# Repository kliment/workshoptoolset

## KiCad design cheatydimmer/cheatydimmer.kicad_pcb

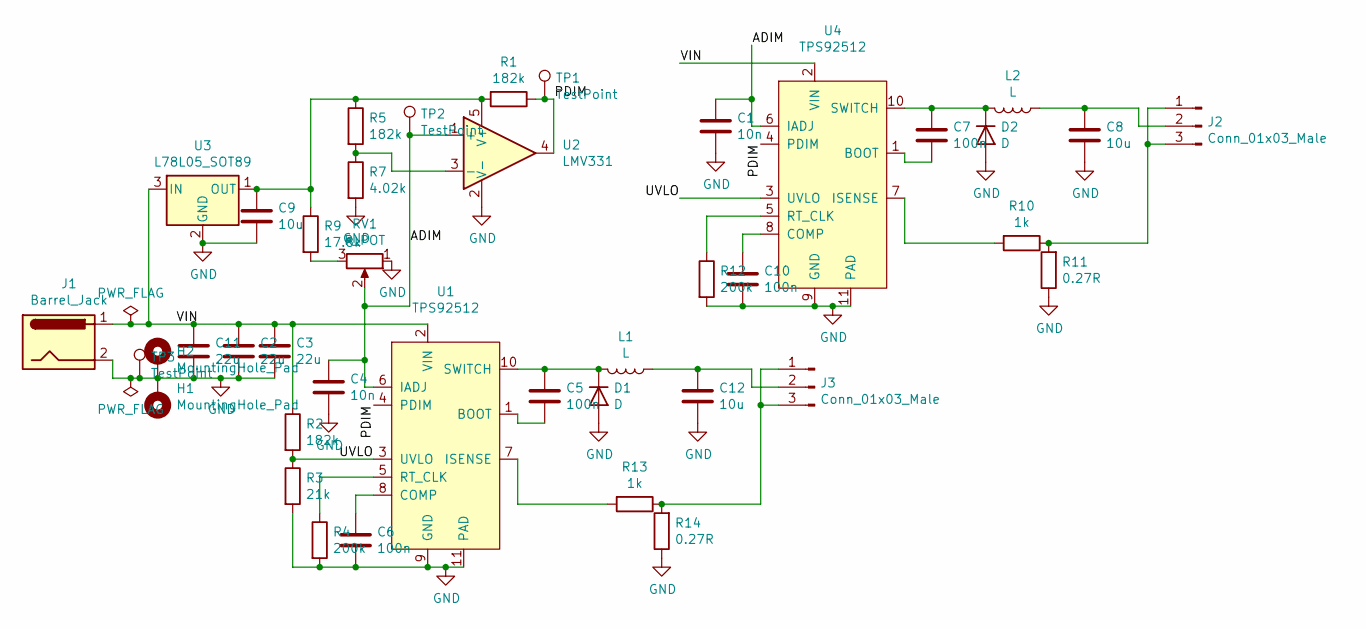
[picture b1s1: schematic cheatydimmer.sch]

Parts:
C1, C4: 10n; C_0603_1608Metric
C2, C3, C11: 22u; C_1206_3216Metric
C5, C6, C7, C10: 100n; C_0603_1608Metric
C8, C9, C12: 10u; C_0805_2012Metric
D1, D2: D; D_SMA
H1, H2: MountingHole_Pad; MountingHole_3.2mm_M3_Pad_Via
J1: Barrel_Jack; BarrelJack_Horizontal
J2, J3: Conn_01x03_Male; PinHeader_1x03_P2.54mm_Vertical
L1, L2: L; L_Sumida_CDMC6D28_7.25x6.5mm
R1, R2, R5: 182k; R_0603_1608Metric
R3: 21k; R_0603_1608Metric
R4, R12: 200k; R_0603_1608Metric
R7: 4.02k; R_0603_1608Metric
R9: 17.8k; R_0603_1608Metric
R10, R13: 1k; R_0603_1608Metric
R11, R14: 0.27R; R_1210_3225Metric
RV1: R_POT; ALPS-RS08U
TP1, TP2, TP3: TestPoint; TestPoint_Pad_1.5x1.5mm
U1, U4: TPS92512; MSOP-10-1EP_3x3mm_P0.5mm_EP1.73x1.98mm_ThermalVias
U2: LMV331; SOT-23-5
U3: L78L05_SOT89; SOT-89-3

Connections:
/ADIM: C1.1, C4.1, RV1.2, TP2.1, U1.6 (IADJ), U2.1 (+), U4.6 (IADJ)
/PDIM: R1.1, TP1.1, U1.4 (PDIM), U2.4, U4.4 (PDIM)
/UVLO: R2.2, R3.1, U1.3 (UVLO), U4.3 (UVLO)
/VIN: C2.1, C3.1, C11.1, J1.1, R2.1, U1.2 (VIN), U3.3 (IN), U4.2 (VIN)
GND: C1.2, C2.2, C3.2, C4.2, C6.2, C8.2, C9.2, C10.2, C11.2, C12.2, D1.2 (A), D2.2 (A), H1.1, H2.1, J1.2, R3.2, R4.2, R7.2, R11.1, R12.2, R14.1, RV1.1, TP3.1, U1.9 (GND), U1.11 (PAD), U2.2 (V-), U3.2 (GND), U4.9 (GND), U4.11 (PAD)
unnamed: C5.1, D1.1 (K), L1.2, U1.10 (SWITCH)
unnamed: C5.2, U1.1 (BOOT)
unnamed: C6.1, U1.8 (COMP)
unnamed: C7.1, D2.1 (K), L2.2, U4.10 (SWITCH)
unnamed: C7.2, U4.1 (BOOT)
unnamed: C8.1, J2.2, L2.1
unnamed: C9.1, R1.2, R5.1, R9.1, U2.5 (V+), U3.1 (OUT)
unnamed: C10.1, U4.8 (COMP)
unnamed: C12.1, J3.2, L1.1
unnamed: J2.1, J2.3, R10.1, R11.2
unnamed: J3.1, J3.3, R13.1, R14.2
unnamed: R4.1, U1.5 (RT_CLK)
unnamed: R5.2, R7.1, U2.3 (-)
unnamed: R9.2, RV1.3
unnamed: R10.2, U4.7 (ISENSE)
unnamed: R12.1, U4.5 (RT_CLK)
unnamed: R13.2, U1.7 (ISENSE)

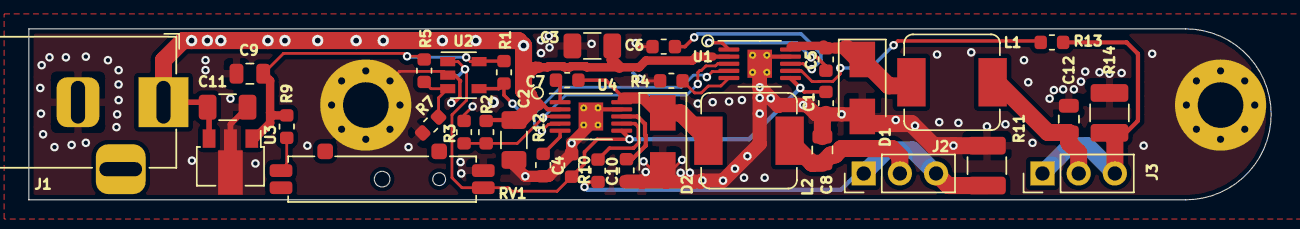
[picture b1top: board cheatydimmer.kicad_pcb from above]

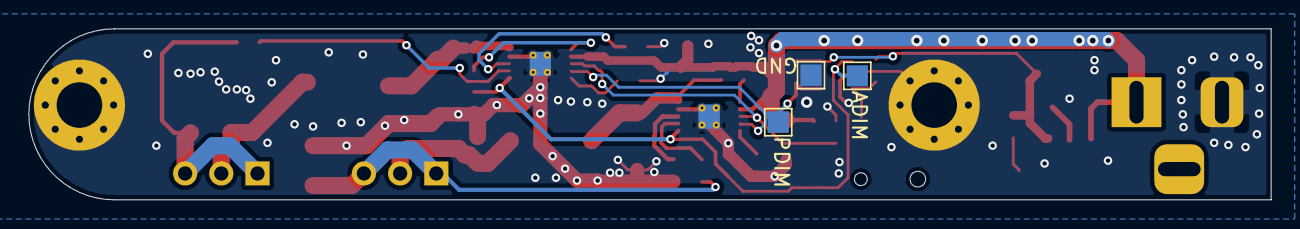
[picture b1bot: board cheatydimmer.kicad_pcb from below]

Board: 2 copper layers, 87.2 x 12.0 mm, 41 parts (3 on the bottom side), 22 nets.

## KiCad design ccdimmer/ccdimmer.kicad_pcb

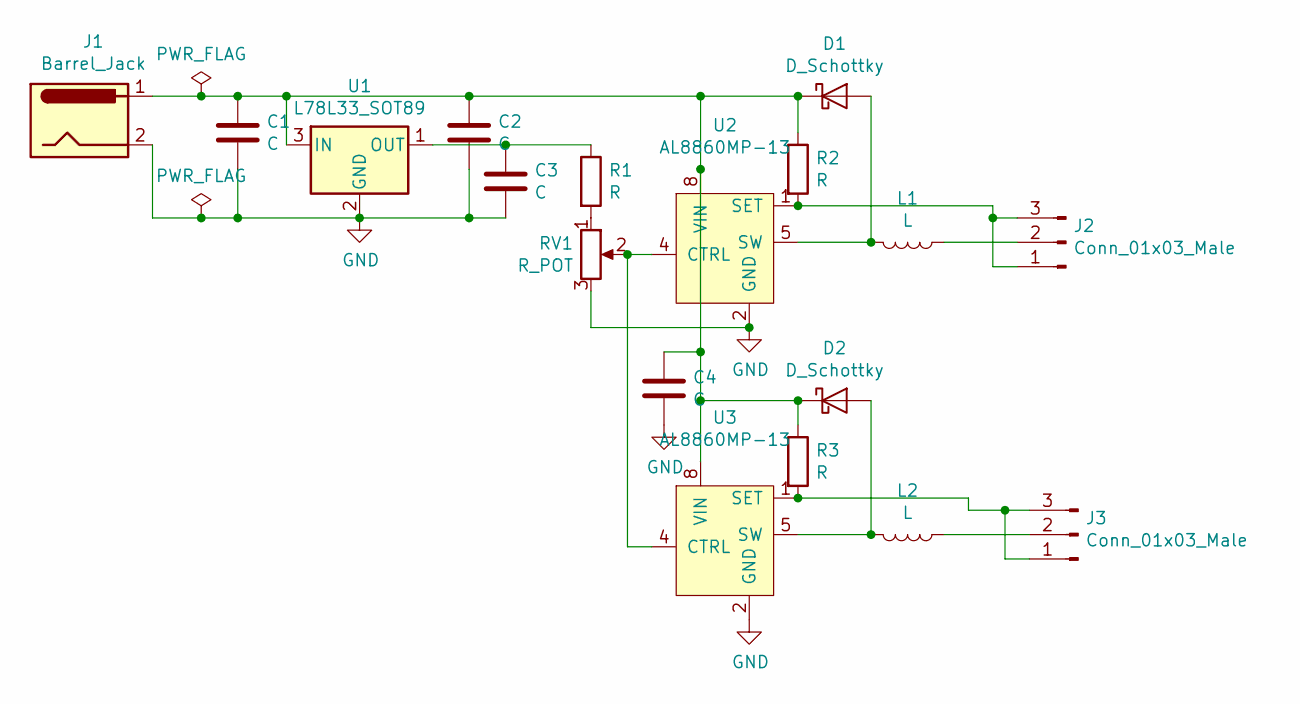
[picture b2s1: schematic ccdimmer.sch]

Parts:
C1, C2, C3, C4: C; C_0805_2012Metric
D1, D2: D_Schottky; D_SMA
J1: Barrel_Jack; BarrelJack_Horizontal
J2, J3: Conn_01x03_Male; PinHeader_1x03_P2.54mm_Vertical
L1, L2: L; L_6.3x6.3_H3
R1: R; R_0603_1608Metric
R2, R3: R; R_1206_3216Metric
RV1: R_POT; ALPS-RS08U
U1: L78L33_SOT89; SOT-89-3
U2, U3: AL8860MP-13; MSOP-8-1EP_3x3mm_P0.65mm_EP1.95x2.15mm

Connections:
GND: C1.2, C2.2, C3.2, C4.2, J1.2, RV1.3, U1.2 (GND), U2.2 (GND), U2.3 (GND), U2.9 (GND), U3.2 (GND), U3.3 (GND), U3.9 (GND)
unnamed: C1.1, C2.1, C4.1, D1.1 (K), D2.1 (K), J1.1, R2.1, R3.1, U1.3 (IN), U2.8 (VIN), U3.8 (VIN)
unnamed: C3.1, R1.1, U1.1 (OUT)
unnamed: D1.2 (A), L1.2, U2.5 (SW), U2.6 (SW)
unnamed: D2.2 (A), L2.2, U3.5 (SW), U3.6 (SW)
unnamed: J2.1, J2.3, R2.2, U2.1 (SET)
unnamed: J2.2, L1.1
unnamed: J3.1, J3.3, R3.2, U3.1 (SET)
unnamed: J3.2, L2.1
unnamed: R1.2, RV1.1
unnamed: RV1.2, U2.4 (CTRL), U3.4 (CTRL)

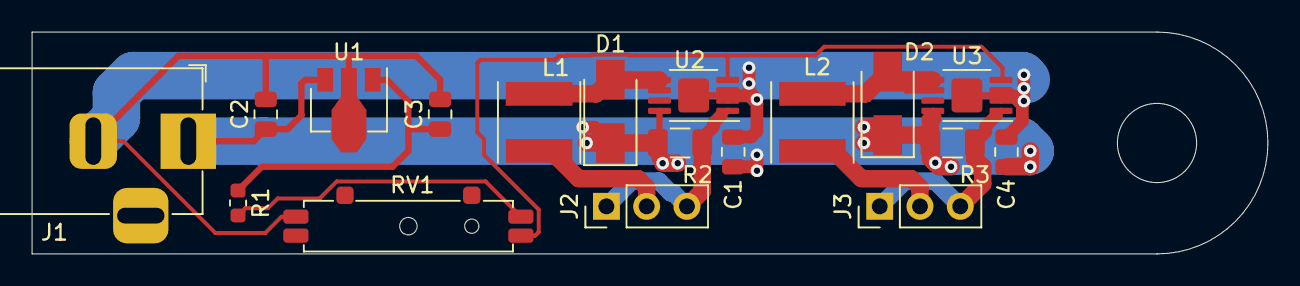
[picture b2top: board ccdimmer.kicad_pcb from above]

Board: 2 copper layers, 78.0 x 14.0 mm, 18 parts (0 on the bottom side), 11 nets.

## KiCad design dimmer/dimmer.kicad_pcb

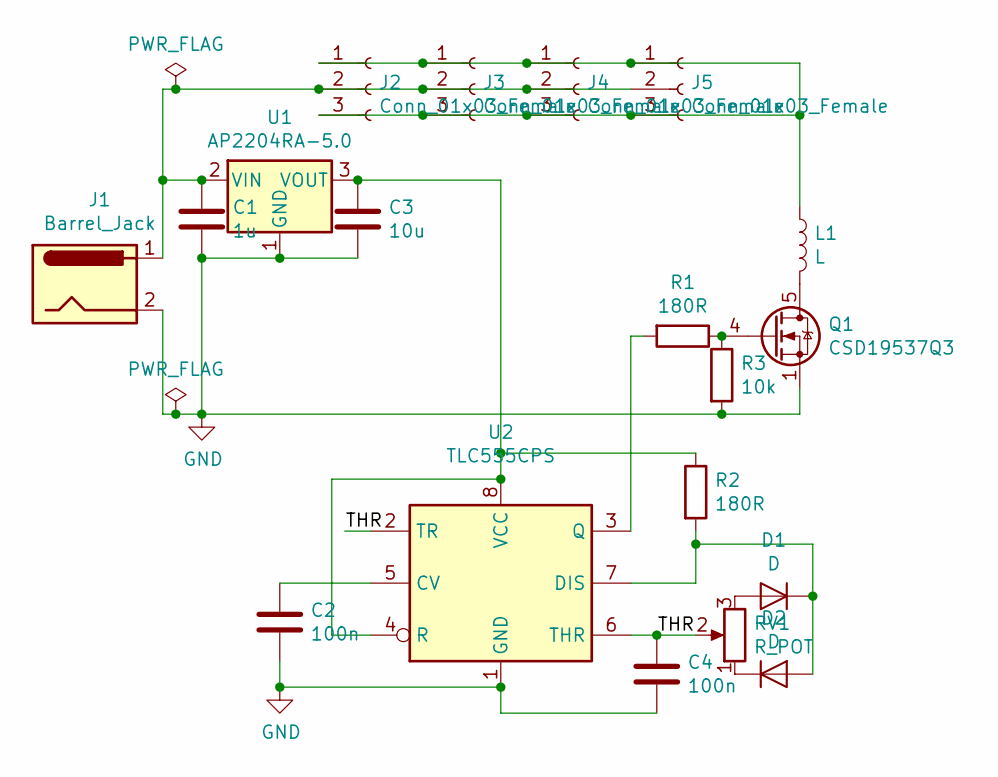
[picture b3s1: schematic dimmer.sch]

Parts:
C1: 1u; C_0603_1608Metric
C2, C4: 100n; C_0402_1005Metric
C3: 10u; C_0402_1005Metric
D1, D2: D; D_SOD-523
J1: Barrel_Jack; BarrelJack_Horizontal
J2, J3, J4, J5: Conn_01x03_Female; PinSocket_1x03_P2.54mm_Vertical
L1: L; INDUCTOR_2x1.6x1mm
Q1: CSD19537Q3; VSON-8_3.3x3.3mm_P0.65mm_NexFET
R1, R2: 180R; R_0603_1608Metric
R3: 10k; R_0603_1608Metric
RV1: R_POT; ALPS-RS08U
U1: AP2204RA-5.0; SOT-89-3
U2: TLC555CPS; TSSOP-8_3x3mm_P0.65mm

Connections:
/THR: C4.1, RV1.2, U2.2 (TR), U2.6 (THR)
GND: C1.2, C2.2, C3.2, C4.2, J1.2, Q1.1 (S), Q1.2 (S), Q1.3 (S), R3.2, U1.1 (GND), U2.1 (GND)
unnamed: C1.1, J1.1, J2.2, J3.2, J4.2, J5.2, U1.2 (VIN)
unnamed: C2.1, U2.5 (CV)
unnamed: C3.1, R2.1, U1.3 (VOUT), U2.4 (R), U2.8 (VCC)
unnamed: D1.1 (K), D2.2 (A), R2.2, U2.7 (DIS)
unnamed: D1.2 (A), RV1.3
unnamed: D2.1 (K), RV1.1
unnamed: J2.1, J2.3, J3.1, J3.3, J4.1, J4.3, J5.1, J5.3, L1.1
unnamed: L1.2, Q1.5 (D)
unnamed: Q1.4 (G), R1.1, R3.1
unnamed: R1.2, U2.3 (Q)

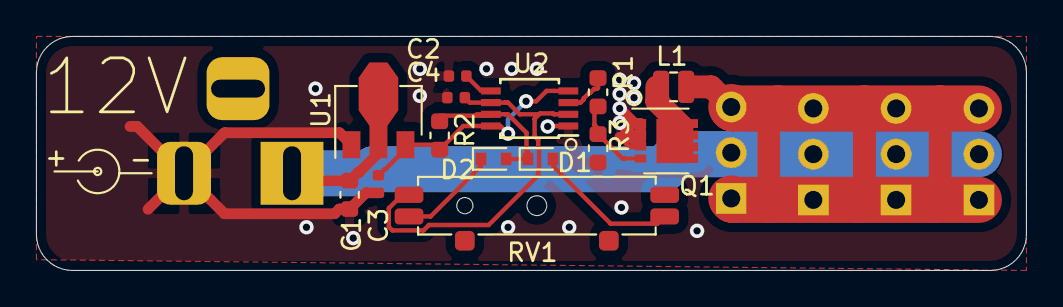
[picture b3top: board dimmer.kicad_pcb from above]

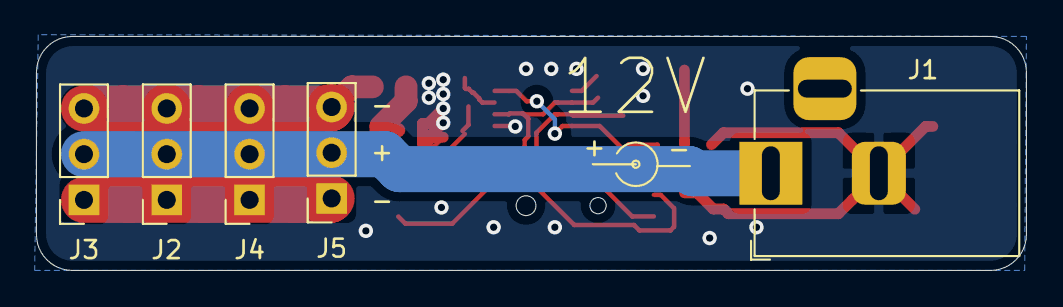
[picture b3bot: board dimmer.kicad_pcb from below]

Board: 2 copper layers, 55.0 x 13.0 mm, 19 parts (5 on the bottom side), 12 nets.

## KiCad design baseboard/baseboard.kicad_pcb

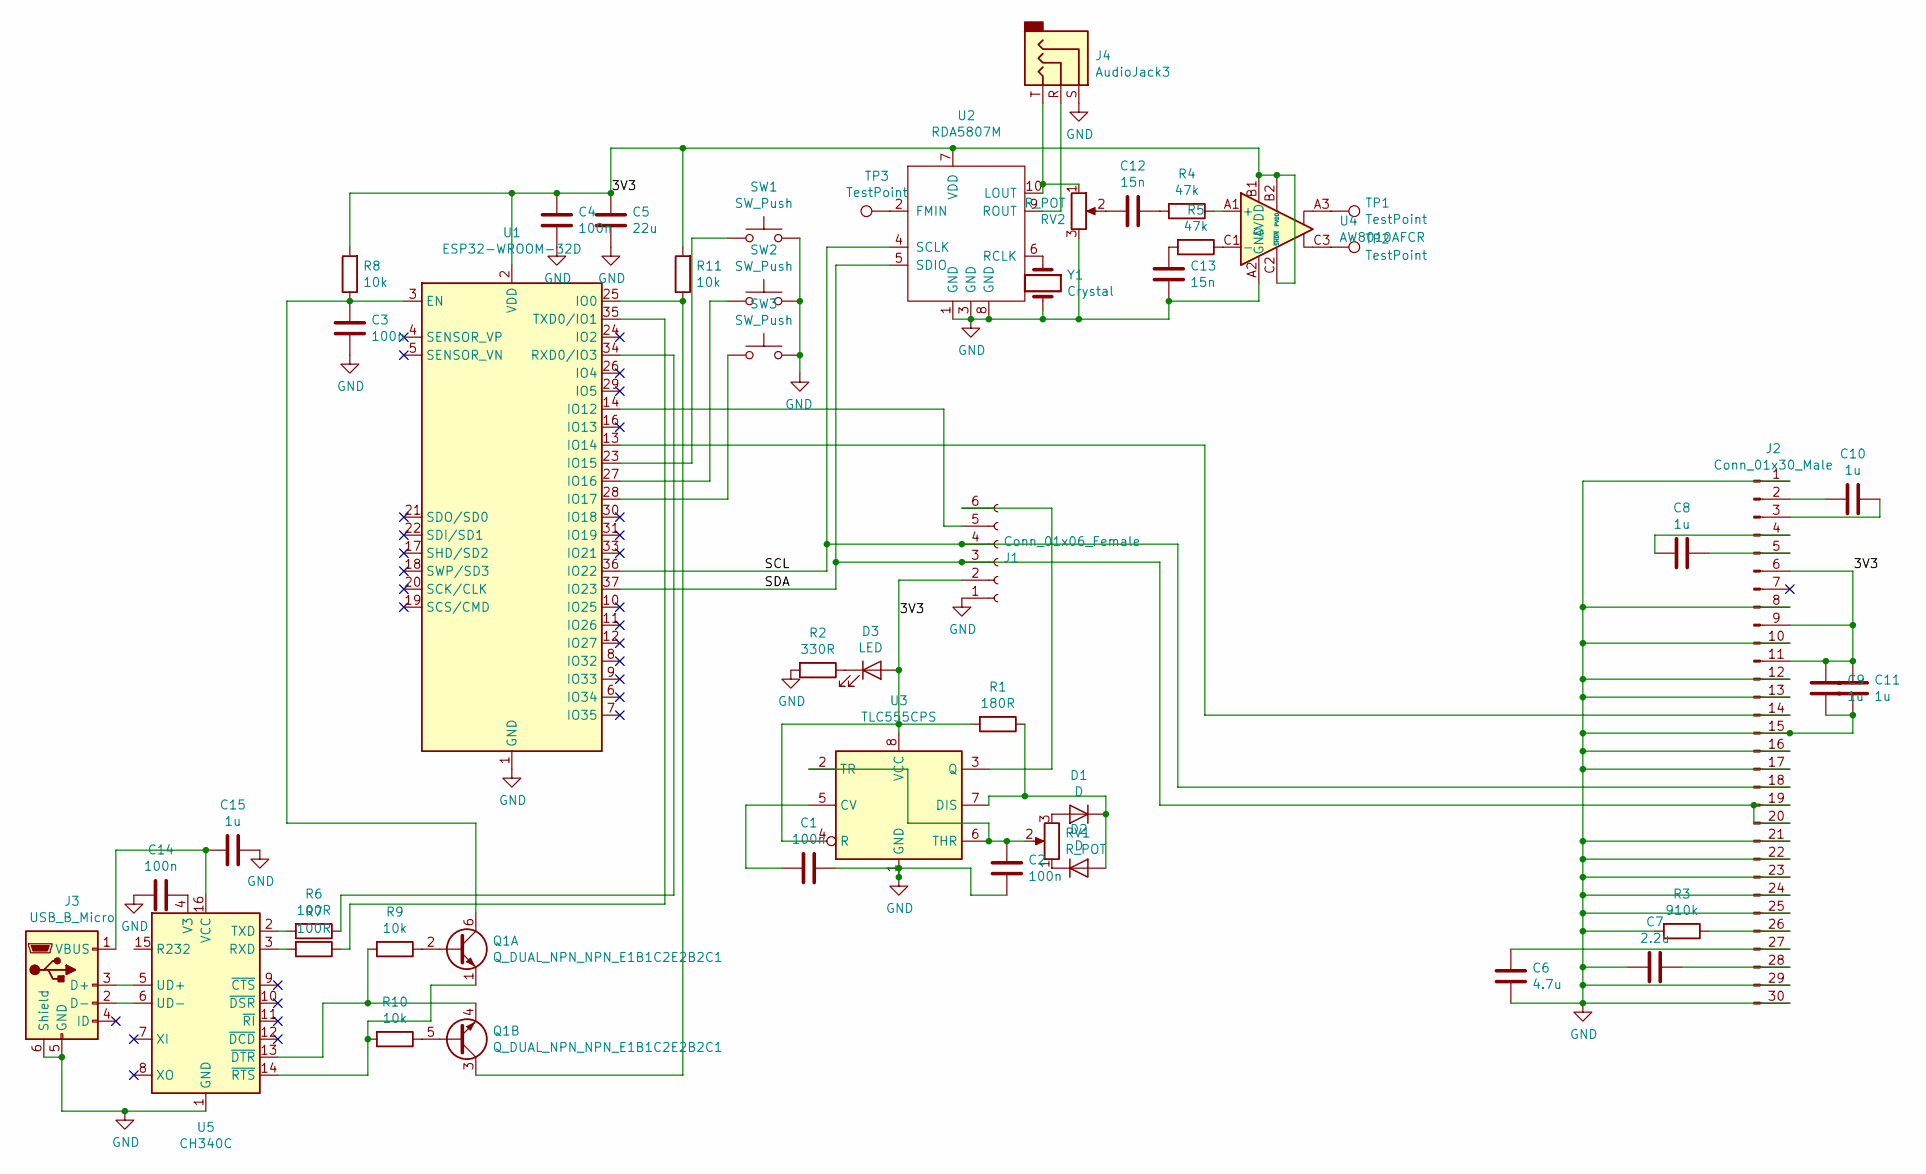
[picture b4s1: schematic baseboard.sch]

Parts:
C1, C2, C3, C4, C14: 100n; C_0402_1005Metric
C5: 22u; C_0603_1608Metric
C6: 4.7u; C_0603_1608Metric
C7: 2.2u; C_0603_1608Metric
C8, C9, C10, C11, C15: 1u; C_0402_1005Metric
C12, C13: 15n; C_0402_1005Metric
D1, D2: D; D_SOD-523
D3: LED; LED_0603_1608Metric
J1: Conn_01x06_Female; PinSocket_1x06_P2.54mm_Horizontal
J2: Conn_01x30_Male; hotbar_30x0.7
J3: USB_B_Micro; USB_Micro-B_Molex-105017-0001
J4: AudioJack3; Boom-audiojack-PJ-320B
Q1: Q_DUAL_NPN_NPN_E1B1C2E2B2C1; SOT-363_SC-70-6
R1: 180R; R_0603_1608Metric
R2: 330R; R_0603_1608Metric
R3: 910k; R_0603_1608Metric
R4, R5: 47k; R_0402_1005Metric
R6, R7: 100R; R_0402_1005Metric
R8, R9, R10, R11: 10k; R_0402_1005Metric
RV1, RV2: R_POT; ALPS-RS08U
SW1, SW2, SW3: SW_Push; 1TS003B-1600-3500A
TP1, TP2, TP3: TestPoint; TestPoint_Pad_3.0x3.0mm
U1: ESP32-WROOM-32D; ESP32-WROOM-32
U2: RDA5807M; MSOP-10_3x3mm_P0.5mm
U3: TLC555CPS; TSSOP-8_4.4x3mm_P0.65mm
U4: AW8010AFCR; Texas_DSBGA-9_1.4715x1.4715mm_Layout3x3_P0.5mm
U5: CH340C; SOIC-16_3.9x9.9mm_P1.27mm
Y1: Crystal; Crystal_SMD_3215-2Pin_3.2x1.5mm

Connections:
/3V3: C4.1, C5.1, C9.1, C11.1, D3.2 (A), J1.2, J2.6, J2.9, J2.11, R1.2, R8.2, R11.2, U1.2 (VDD), U2.7 (VDD), U3.4 (R), U3.8 (VCC), U4.B1 (AVDD), U4.B2 (PVDD), U4.C2 (~SHDN)
/SCL: J1.4, J2.18, U1.36 (IO22), U2.4 (SCLK)
/SDA: J1.3, J2.19, J2.20, U1.37 (IO23), U2.5 (SDIO)
GND: C1.1, C2.2, C3.2, C4.2, C5.2, C6.2, C7.2, C9.2, C11.2, C13.1, C14.2, C15.1, J1.1, J2.1, J2.8, J2.10, J2.12, J2.13, J2.15, J2.16, J2.17, J2.21, J2.22, J2.23, J2.24, J2.25, J2.29, J2.30, J3.5 (GND), J3.6 (Shield), J4.S, R2.2, R3.2, RV2.3, SW1.1, SW2.1, SW3.1, U1.1 (GND), U1.15 (GND), U1.38 (GND), U2.1 (GND), U2.3 (GND), U2.8 (GND), U3.1 (GND), U4.A2 (GND), U4.B3 (GND), U5.1 (GND), Y1.2
unnamed: C1.2, U3.5 (CV)
unnamed: C2.1, RV1.2, U3.2 (TR), U3.6 (THR)
unnamed: C3.1, Q1.6 (C1), R8.1, U1.3 (EN)
unnamed: C6.1, J2.27
unnamed: C7.1, J2.28
unnamed: C8.1, J2.5
unnamed: C8.2, J2.4
unnamed: C10.1, J2.3
unnamed: C10.2, J2.2
unnamed: C12.1, R4.2
unnamed: C12.2, RV2.2
unnamed: C13.2, R5.2
unnamed: C14.1, U5.4 (V3)
unnamed: C15.2, J3.1 (VBUS), U5.16 (VCC)
unnamed: D1.1 (K), D2.2 (A), R1.1, U3.7 (DIS)
unnamed: D1.2 (A), RV1.3
unnamed: D2.1 (K), RV1.1
unnamed: D3.1 (K), R2.1
unnamed: J1.5, U1.14 (IO12)
unnamed: J1.6, U3.3 (Q)
unnamed: J2.14, U1.13 (IO14)
unnamed: J2.26, R3.1
unnamed: J3.2 (D-), U5.6 (UD-)
unnamed: J3.3 (D+), U5.5 (UD+)
unnamed: J4.R, U2.9 (ROUT)
unnamed: J4.T, RV2.1, U2.10 (LOUT)
unnamed: Q1.1 (E1), R10.2, U5.14 (~RTS)
unnamed: Q1.2 (B1), R9.1
unnamed: Q1.3 (C2), R11.1, U1.25 (IO0)
unnamed: Q1.4 (E2), R9.2, U5.13 (~DTR)
unnamed: Q1.5 (B2), R10.1
unnamed: R4.1, U4.A1 (+)
unnamed: R5.1, U4.C1 (-)
unnamed: R6.1, U1.34 (RXD0/IO3)
unnamed: R6.2, U5.2 (TXD)
unnamed: R7.1, U1.35 (TXD0/IO1)
unnamed: R7.2, U5.3 (RXD)
unnamed: SW1.2, U1.23 (IO15)
unnamed: SW2.2, U1.27 (IO16)
unnamed: SW3.2, U1.28 (IO17)
unnamed: TP1.1, U4.A3
unnamed: TP2.1, U4.C3
unnamed: TP3.1, U2.2 (FMIN)
unnamed: U2.6 (RCLK), Y1.1

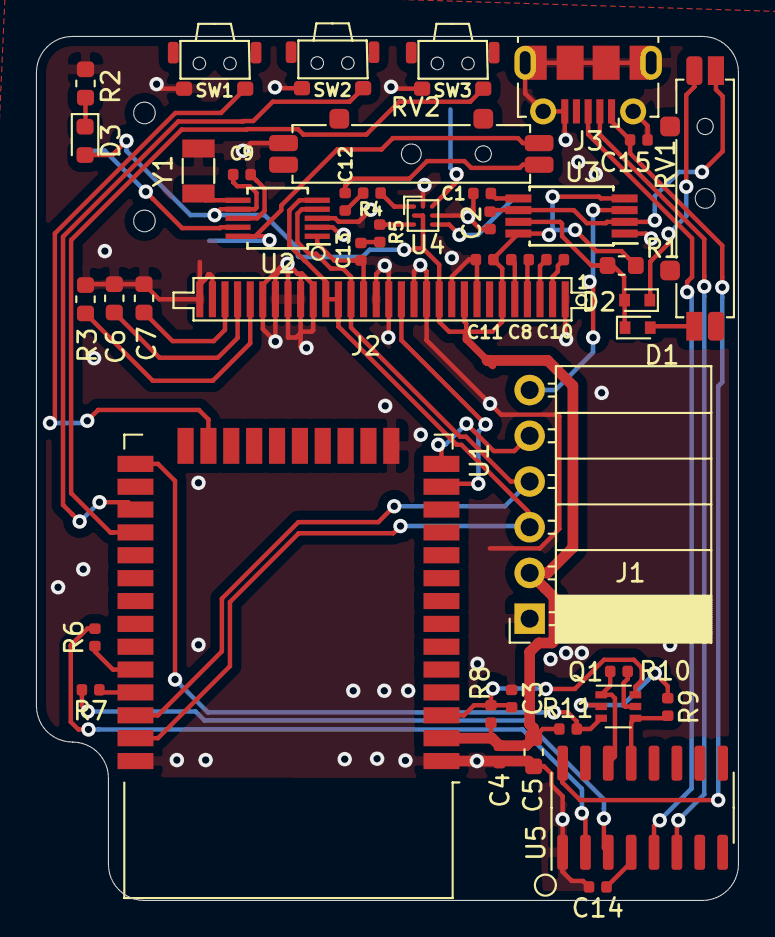
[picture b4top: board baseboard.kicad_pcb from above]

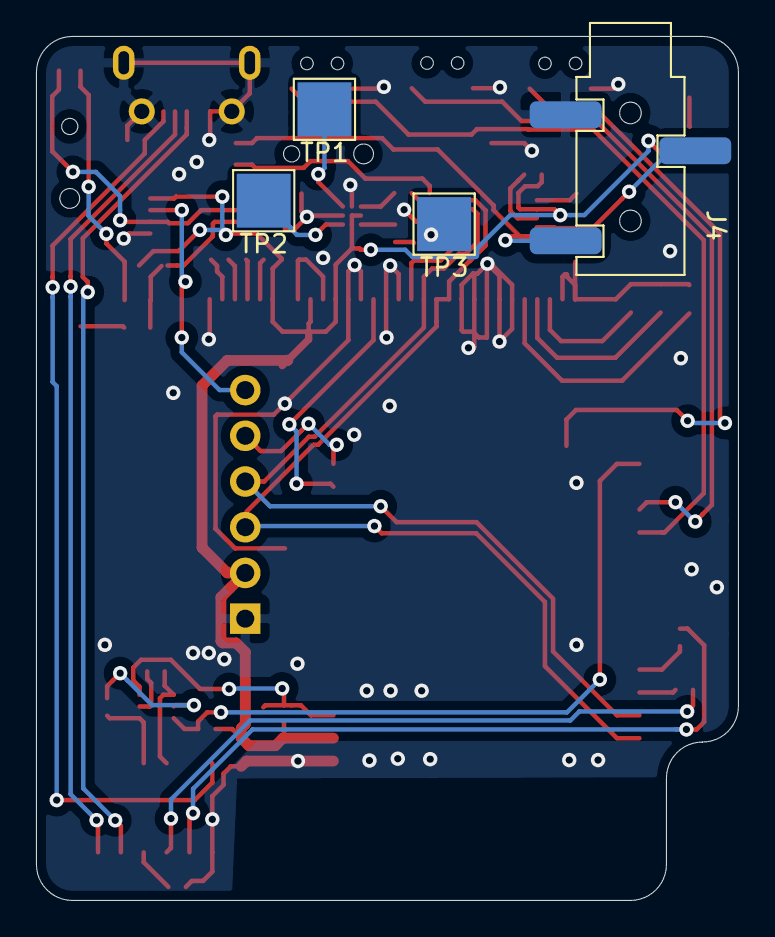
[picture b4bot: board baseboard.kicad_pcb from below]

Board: 2 copper layers, 39.0 x 48.0 mm, 48 parts (4 on the bottom side), 48 nets.

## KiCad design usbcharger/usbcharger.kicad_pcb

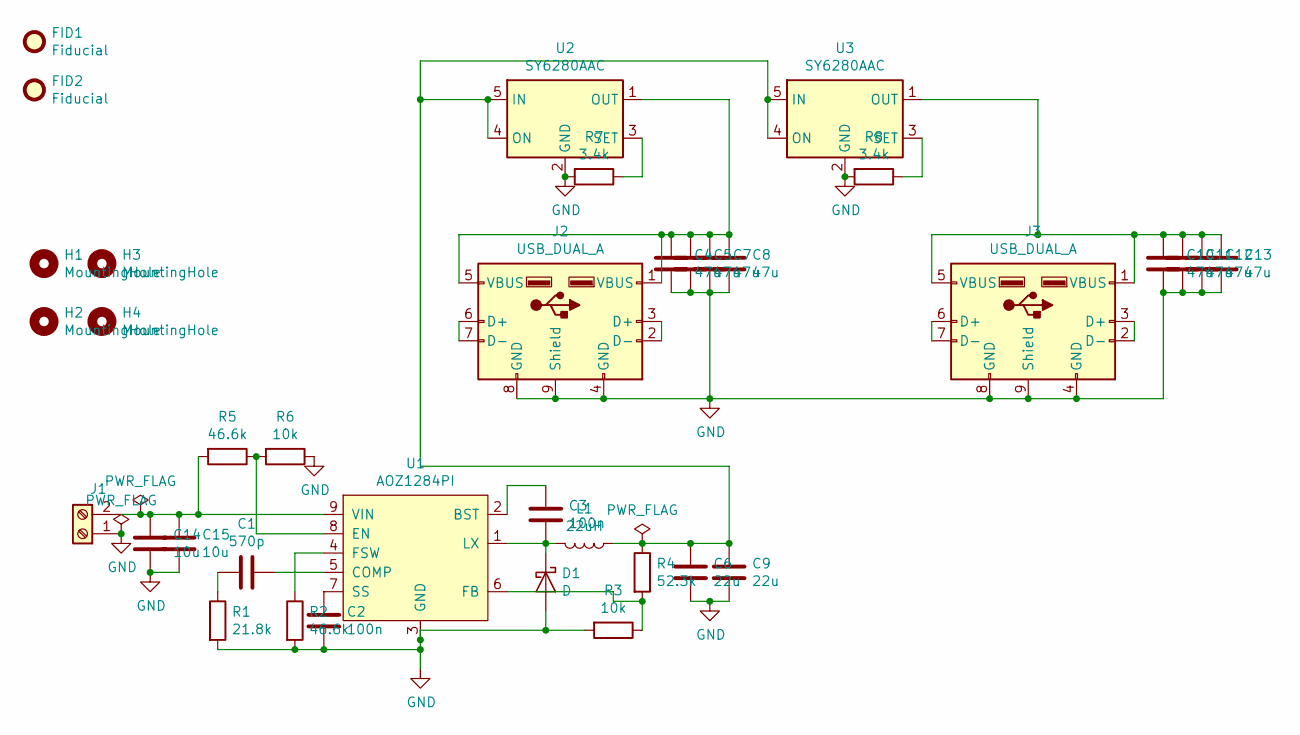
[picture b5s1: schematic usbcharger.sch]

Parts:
C1: 570p; C_0402_1005Metric
C2, C3: 100n; C_0402_1005Metric
C4, C5, C7, C8, C10, C11, C12, C13: 47u; C_1206_3216Metric
C6, C9: 22u; C_1206_3216Metric
C14, C15: 10u; C_1210_3225Metric
D1: D; D_SMA
FID1, FID2: Fiducial; Fiducial_1mm_Mask2mm
H1, H2, H3, H4: MountingHole; MountingHole_3.2mm_M3_DIN965
J1: Screw_Terminal_01x02; TerminalBlock_Phoenix_MKDS-1,5-2-5.08_1x02_P5.08mm_Horizont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
J2, J3: USB_DUAL_A; USB_A_Wuerth_61400826021_Horizontal_Stacked
L1: 22uH; L_7.3x7.3_H3.5
R1: 21.8k; R_0402_1005Metric
R2, R5: 46.6k; R_0402_1005Metric
R3, R6: 10k; R_0402_1005Metric
R4: 52.3k; R_0402_1005Metric
R7, R8: 3.4k; R_0402_1005Metric
U1: AOZ1284PI; Infineon_PG-DSO-8-43
U2, U3: SY6280AAC; SOT-23-5

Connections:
GND: C2.2, C4.2, C5.2, C6.2, C7.2, C8.2, C9.2, C10.2, C11.2, C12.2, C13.2, C14.2, C15.2, D1.2 (A), J1.1, J2.4 (GND), J2.8 (GND), J2.9 (Shield), J3.4 (GND), J3.8 (GND), J3.9 (Shield), R1.2, R2.2, R3.2, R6.1, R7.2, R8.2, U1.3 (GND), U2.2 (GND), U3.2 (GND)
unnamed: C1.1, U1.5 (COMP)
unnamed: C1.2, R1.1
unnamed: C2.1, U1.7 (SS)
unnamed: C3.1, U1.2 (BST)
unnamed: C3.2, D1.1 (K), L1.2, U1.1 (LX)
unnamed: C4.1, C5.1, C7.1, C8.1, J2.1 (VBUS), J2.5 (VBUS), U2.1 (OUT)
unnamed: C6.1, C9.1, L1.1, R4.1, U2.4 (ON), U2.5 (IN), U3.4 (ON), U3.5 (IN)
unnamed: C10.1, C11.1, C12.1, C13.1, J3.1 (VBUS), J3.5 (VBUS), U3.1 (OUT)
unnamed: C14.1, C15.1, J1.2, R5.2, U1.9 (VIN)
unnamed: J2.2 (D-), J2.3 (D+)
unnamed: J2.6 (D+), J2.7 (D-)
unnamed: J3.2 (D-), J3.3 (D+)
unnamed: J3.6 (D+), J3.7 (D-)
unnamed: R2.1, U1.4 (FSW)
unnamed: R3.1, R4.2, U1.6 (FB)
unnamed: R5.1, R6.2, U1.8 (EN)
unnamed: R7.1, U2.3 (SET)
unnamed: R8.1, U3.3 (SET)

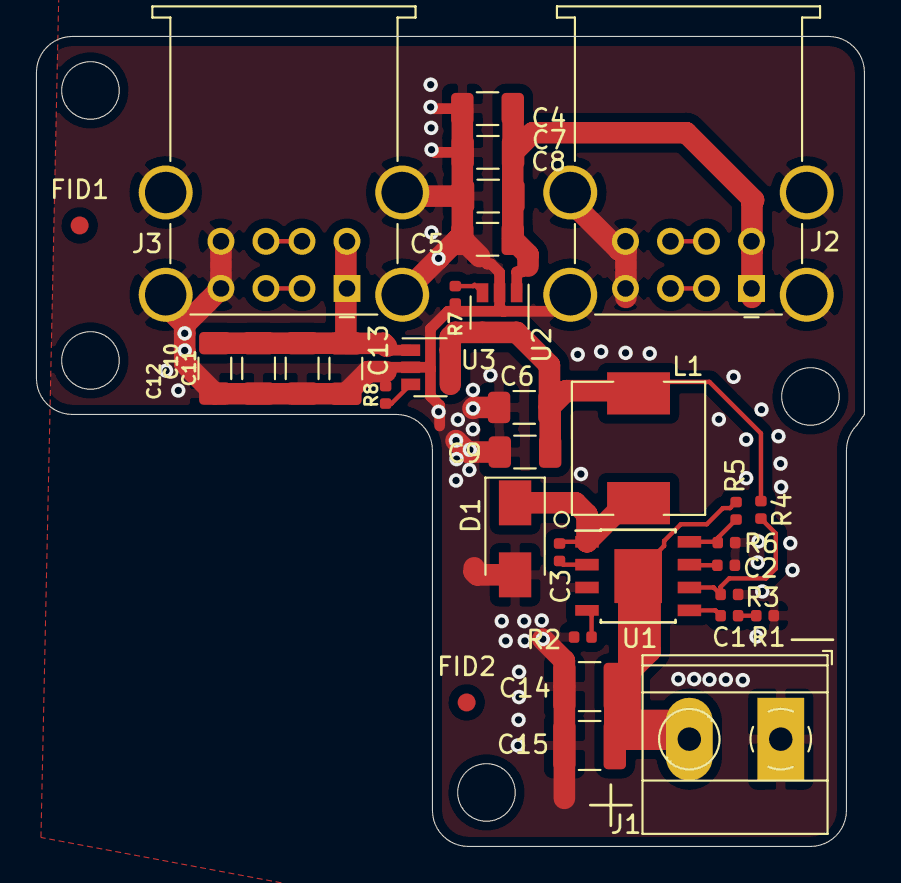
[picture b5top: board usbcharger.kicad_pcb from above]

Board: 2 copper layers, 46.0 x 45.0 mm, 37 parts (0 on the bottom side), 19 nets.

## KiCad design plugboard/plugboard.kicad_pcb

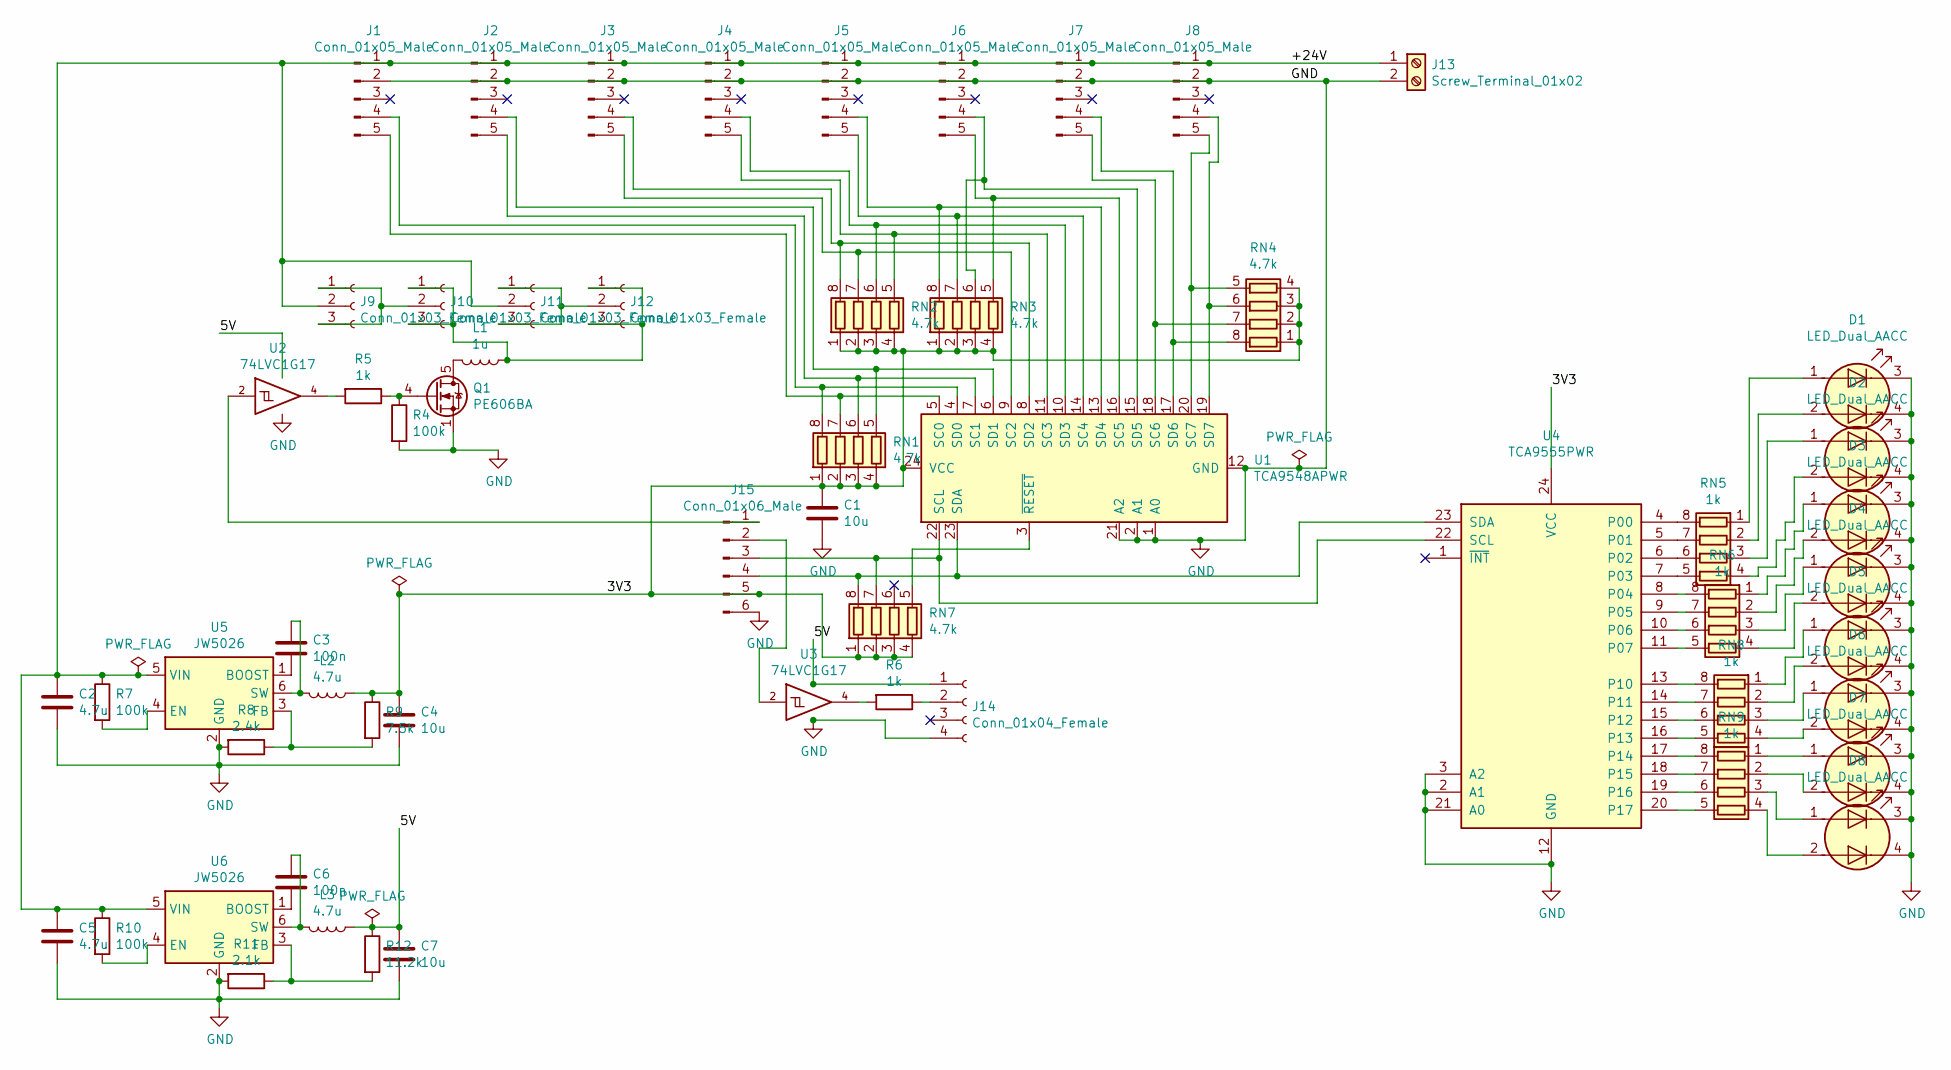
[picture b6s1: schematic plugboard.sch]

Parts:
C1, C4, C7: 10u; C_0603_1608Metric
C2, C5: 4.7u; C_0603_1608Metric
C3, C6: 100n; C_0603_1608Metric
D1, D2, D3, D4, D5, D6, D7, D8: LED_Dual_AACC; LTST-C295KGKRKT
J1, J2, J3, J4, J5, J6, J7, J8: Conn_01x05_Male; PhoenixContact_MCV_1,5_5-G-3.81_1x05_P3.81mm_Vertical
J9, J10, J11, J12: Conn_01x03_Female; PinSocket_1x03_P2.54mm_Vertical
J13: Screw_Terminal_01x02; PhoenixContact_MCV_1,5_2-G-5.08_1x02_P5.08mm_Vertical
J14: Conn_01x04_Female; PinSocket_1x04_P2.54mm_Vertical
J15: Conn_01x06_Male; PinHeader_1x06_P2.54mm_Vertical
L1: 1u; INDUCTOR_2x1.6x1mm
L2, L3: 4.7u; INDUCTOR_2x1.6x1mm
Q1: PE606BA; VSON-8_3.3x3.3mm_P0.65mm_NexFET
R4, R7, R10: 100k; R_0603_1608Metric
R5, R6: 1k; R_0603_1608Metric
R8: 2.4k; R_0603_1608Metric
R9: 7.5k; R_0603_1608Metric
R11: 2.1k; R_0603_1608Metric
R12: 11.2k; R_0603_1608Metric
RN1, RN2, RN3, RN4, RN7: 4.7k; R_Array_Convex_4x0603
RN5, RN6, RN8, RN9: 1k; R_Array_Convex_4x0603
U1: TCA9548APWR; TSSOP-24_4.4x7.8mm_P0.65mm
U2, U3: 74LVC1G17; SOT-353_SC-70-5
U4: TCA9555PWR; TSSOP-24_4.4x7.8mm_P0.65mm
U5, U6: JW5026; TSOT-23-6

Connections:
/3V3: C1.1, C4.1, J15.5, L2.1, R9.1, RN1.1 (R1.1), RN1.2 (R2.1), RN1.3 (R3.1), RN1.4 (R4.1), RN2.1 (R1.1), RN2.2 (R2.1), RN2.3 (R3.1), RN2.4 (R4.1), RN3.1 (R1.1), RN3.2 (R2.1), RN3.3 (R3.1), RN3.4 (R4.1), RN4.1 (R1.1), RN4.2 (R2.1), RN4.3 (R3.1), RN4.4 (R4.1), RN7.1 (R1.1), RN7.2 (R2.1), RN7.3 (R3.1), RN7.4 (R4.1), U1.24 (VCC), U4.24 (VCC)
/+24V: C2.1, C5.1, J1.1, J2.1, J3.1, J4.1, J5.1, J6.1, J7.1, J8.1, J9.2, J11.2, J13.1, R7.1, R10.1, U5.5 (VIN), U6.5 (VIN)
GND: C1.2, C2.2, C4.2, C5.2, C7.2, D1.3 (K1), D1.4 (K2), D2.3 (K1), D2.4 (K2), D3.3 (K1), D3.4 (K2), D4.3 (K1), D4.4 (K2), D5.3 (K1), D5.4 (K2), D6.3 (K1), D6.4 (K2), D7.3 (K1), D7.4 (K2), D8.3 (K1), D8.4 (K2), J1.2, J2.2, J3.2, J4.2, J5.2, J6.2, J7.2, J8.2, J13.2, J14.4, J15.6, Q1.1 (S), Q1.2 (S), Q1.3 (S), R4.2, R8.2, R11.2, U1.1 (A0), U1.2 (A1), U1.12 (GND), U1.21 (A2), U2.3 (GND), U3.3 (GND), U4.2 (A1), U4.3 (A2), U4.12 (GND), U4.21 (A0), U5.2 (GND), U6.2 (GND)
unnamed: C3.1, L2.2, U5.6 (SW)
unnamed: C3.2, U5.1 (BOOST)
unnamed: C6.1, L3.2, U6.6 (SW)
unnamed: C6.2, U6.1 (BOOST)
unnamed: D1.1 (A1), RN5.1 (R1.1)
unnamed: D1.2 (A2), RN5.2 (R2.1)
unnamed: D2.1 (A1), RN5.3 (R3.1)
unnamed: D2.2 (A2), RN5.4 (R4.1)
unnamed: D3.1 (A1), RN6.1 (R1.1)
unnamed: D3.2 (A2), RN6.2 (R2.1)
unnamed: D4.1 (A1), RN6.3 (R3.1)
unnamed: D4.2 (A2), RN6.4 (R4.1)
unnamed: D5.1 (A1), RN8.1 (R1.1)
unnamed: D5.2 (A2), RN8.2 (R2.1)
unnamed: D6.1 (A1), RN8.3 (R3.1)
unnamed: D6.2 (A2), RN8.4 (R4.1)
unnamed: D7.1 (A1), RN9.1 (R1.1)
unnamed: D7.2 (A2), RN9.2 (R2.1)
unnamed: D8.1 (A1), RN9.3 (R3.1)
unnamed: D8.2 (A2), RN9.4 (R4.1)
unnamed: J1.4, RN1.8 (R1.2), U1.4 (SD0)
unnamed: J1.5, RN1.7 (R2.2), U1.5 (SC0)
unnamed: J2.4, RN1.5 (R4.2), U1.6 (SD1)
unnamed: J2.5, RN1.6 (R3.2), U1.7 (SC1)
unnamed: J3.4, RN2.8 (R1.2), U1.8 (SD2)
unnamed: J3.5, RN2.7 (R2.2), U1.9 (SC2)
unnamed: J4.4, RN2.6 (R3.2), U1.10 (SD3)
unnamed: J4.5, RN2.5 (R4.2), U1.11 (SC3)
unnamed: J5.4, RN3.8 (R1.2), U1.13 (SD4)
unnamed: J5.5, RN3.7 (R2.2), U1.14 (SC4)
unnamed: J6.4, RN3.6 (R3.2), U1.15 (SD5)
unnamed: J6.5, RN3.5 (R4.2), U1.16 (SC5)
unnamed: J7.4, RN4.8 (R1.2), U1.17 (SD6)
unnamed: J7.5, RN4.7 (R2.2), U1.18 (SC6)
unnamed: J8.4, RN4.6 (R3.2), U1.19 (SD7)
unnamed: J8.5, RN4.5 (R4.2), U1.20 (SC7)
unnamed: J10.1, J10.3, J12.1, J12.3, L1.1
unnamed: J9.1, J9.3, J10.2
unnamed: J11.1, J11.3, J12.2
unnamed: J14.2, R6.1
unnamed: J15.1, U2.2
unnamed: J15.2, U3.2
unnamed: J15.3, RN7.7 (R2.2), U1.22 (SCL), U4.22 (SCL)
unnamed: J15.4, RN7.8 (R1.2), U1.23 (SDA), U4.23 (SDA)
unnamed: L1.2, Q1.5 (D)
unnamed: Q1.4 (G), R4.1, R5.1
unnamed: R5.2, U2.4
unnamed: R6.2, U3.4
unnamed: R7.2, U5.4 (EN)
unnamed: R8.1, R9.2, U5.3 (FB)
unnamed: R10.2, U6.4 (EN)
unnamed: R11.1, R12.2, U6.3 (FB)
unnamed: RN5.5 (R4.2), U4.7 (P03)
unnamed: RN5.6 (R3.2), U4.6 (P02)
unnamed: RN5.7 (R2.2), U4.5 (P01)
unnamed: RN5.8 (R1.2), U4.4 (P00)
unnamed: RN6.5 (R4.2), U4.11 (P07)
unnamed: RN6.6 (R3.2), U4.10 (P06)
unnamed: RN6.7 (R2.2), U4.9 (P05)
unnamed: RN6.8 (R1.2), U4.8 (P04)
unnamed: RN7.5 (R4.2), U1.3 (~RESET)
unnamed: RN8.5 (R4.2), U4.16 (P13)
unnamed: RN8.6 (R3.2), U4.15 (P12)
unnamed: RN8.7 (R2.2), U4.14 (P11)
unnamed: RN8.8 (R1.2), U4.13 (P10)
unnamed: RN9.5 (R4.2), U4.20 (P17)
unnamed: RN9.6 (R3.2), U4.19 (P16)
unnamed: RN9.7 (R2.2), U4.18 (P15)
unnamed: RN9.8 (R1.2), U4.17 (P14)
VCC: C7.1, J14.1, L3.1, R12.1, U2.5 (VCC), U3.5 (VCC)

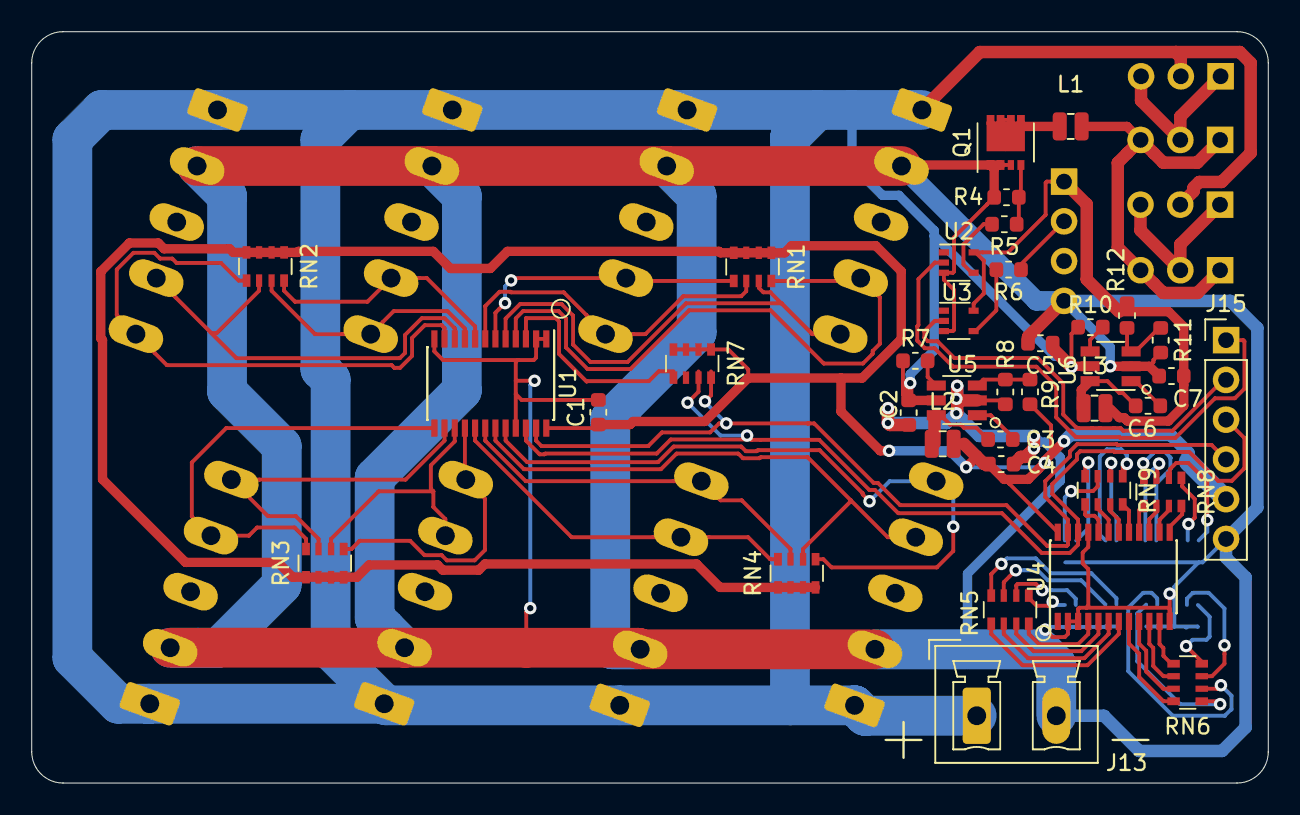
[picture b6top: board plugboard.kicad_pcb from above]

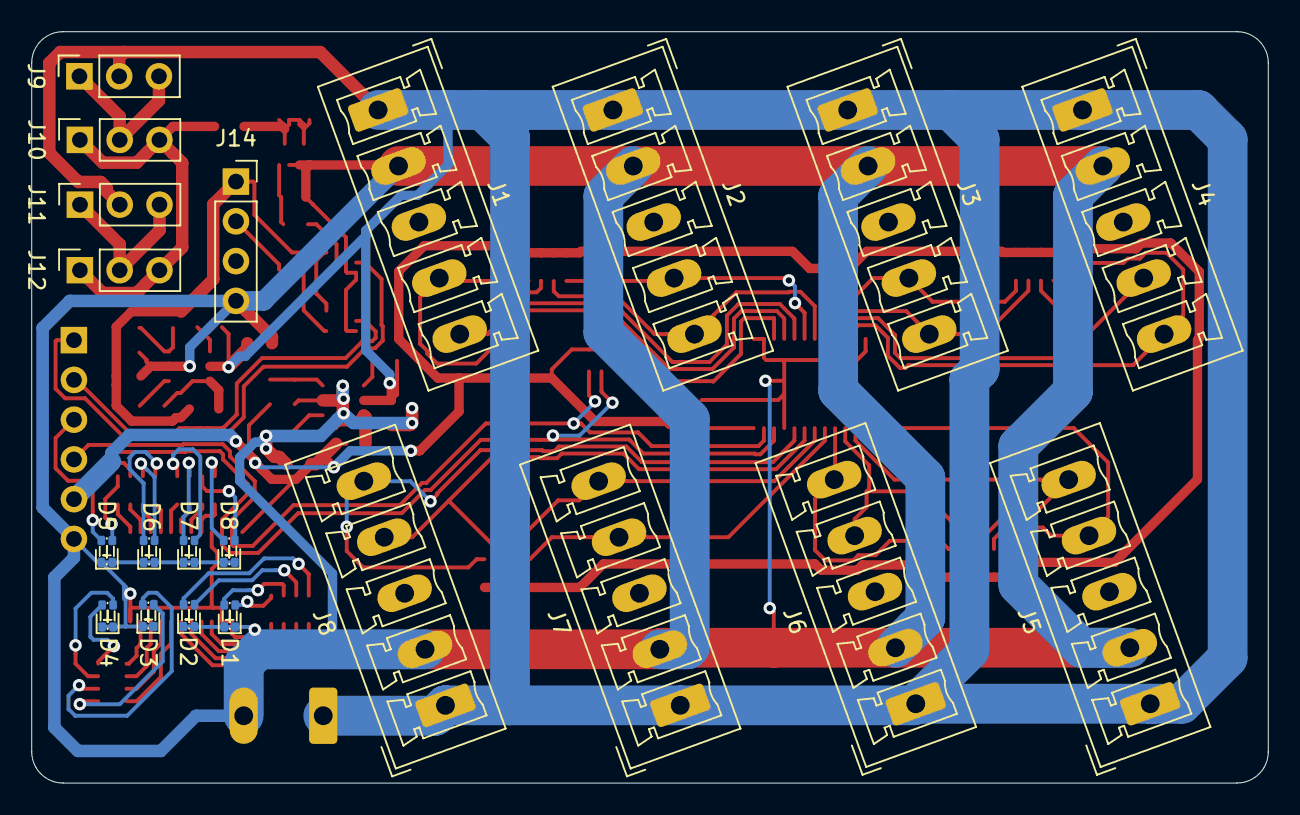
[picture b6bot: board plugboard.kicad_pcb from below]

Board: 2 copper layers, 79.0 x 48.0 mm, 58 parts (21 on the bottom side), 73 nets.

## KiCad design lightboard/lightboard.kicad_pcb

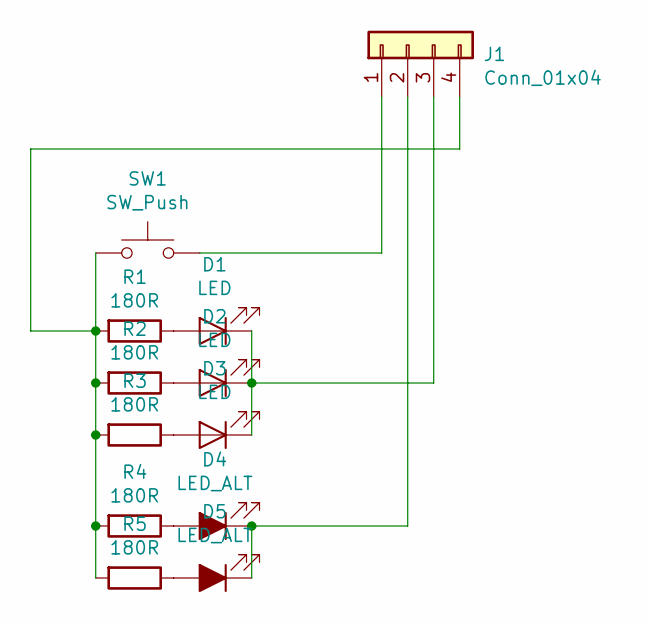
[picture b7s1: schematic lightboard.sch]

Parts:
D1, D2, D3: LED; LED_0603_1608Metric
D4, D5: LED_ALT; LED_0603_1608Metric_Castellated
J1: Conn_01x04; FPC_4_0.5-THD0509-04CL-GF
R1, R2, R3, R4, R5: 180R; R_0603_1608Metric
SW1: SW_Push; 1TS003B-1600-3500A

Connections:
unnamed: D1.1 (K), D2.1 (K), D3.1 (K), J1.3
unnamed: D1.2 (A), R1.1
unnamed: D2.2 (A), R2.1
unnamed: D3.2 (A), R3.1
unnamed: D4.1 (K), D5.1 (K), J1.2
unnamed: D4.2 (A), R4.1
unnamed: D5.2 (A), R5.1
unnamed: J1.1, SW1.2
unnamed: J1.4, R1.2, R2.2, R3.2, R4.2, R5.2, SW1.1
